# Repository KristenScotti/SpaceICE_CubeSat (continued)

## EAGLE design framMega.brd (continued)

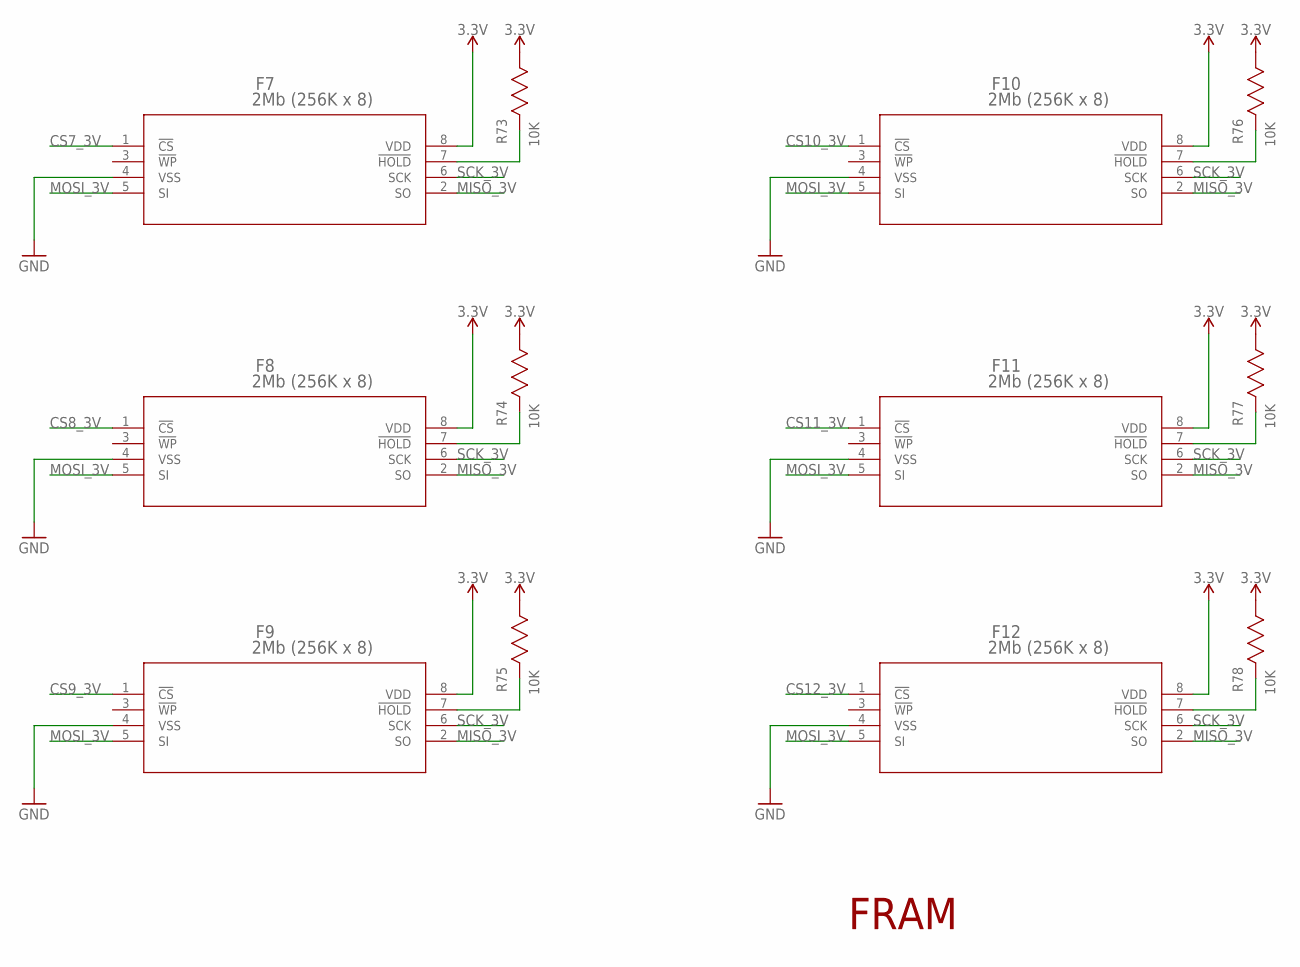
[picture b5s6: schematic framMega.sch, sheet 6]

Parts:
F7, F8, F9, F10, F11, F12: 2Mb (256K x 8); FRAM_MB85RS2MTA_FPT-8P-M09
R73, R74, R75, R76, R77, R78: 10K; RC0603N

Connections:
3.3V: F7.8 (VDD), F8.8 (VDD), F9.8 (VDD), F10.8 (VDD), F11.8 (VDD), F12.8 (VDD), R73.1 (11), R74.1 (11), R75.1 (11), R76.1 (11), R77.1 (11), R78.1 (11); also elsewhere on the board
CS7_3V: F7.1 (!CS); also elsewhere on the board
CS8_3V: F8.1 (!CS); also elsewhere on the board
CS9_3V: F9.1 (!CS); also elsewhere on the board
CS10_3V: F10.1 (!CS); also elsewhere on the board
CS11_3V: F11.1 (!CS); also elsewhere on the board
CS12_3V: F12.1 (!CS); also elsewhere on the board
GND: F7.4 (VSS), F8.4 (VSS), F9.4 (VSS), F10.4 (VSS), F11.4 (VSS), F12.4 (VSS); also elsewhere on the board
MISO_3V: F7.2 (SO), F8.2 (SO), F9.2 (SO), F10.2 (SO), F11.2 (SO), F12.2 (SO); also elsewhere on the board
MOSI_3V: F7.5 (SI), F8.5 (SI), F9.5 (SI), F10.5 (SI), F11.5 (SI), F12.5 (SI); also elsewhere on the board
unnamed: F7.7 (!HOLD), R73.2 (22)
unnamed: F10.7 (!HOLD), R76.2 (22)
unnamed: F8.7 (!HOLD), R74.2 (22)
unnamed: F11.7 (!HOLD), R77.2 (22)
unnamed: F9.7 (!HOLD), R75.2 (22)
unnamed: F12.7 (!HOLD), R78.2 (22)
SCK_3V: F7.6 (SCK), F8.6 (SCK), F9.6 (SCK), F10.6 (SCK), F11.6 (SCK), F12.6 (SCK); also elsewhere on the board

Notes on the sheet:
FRAM

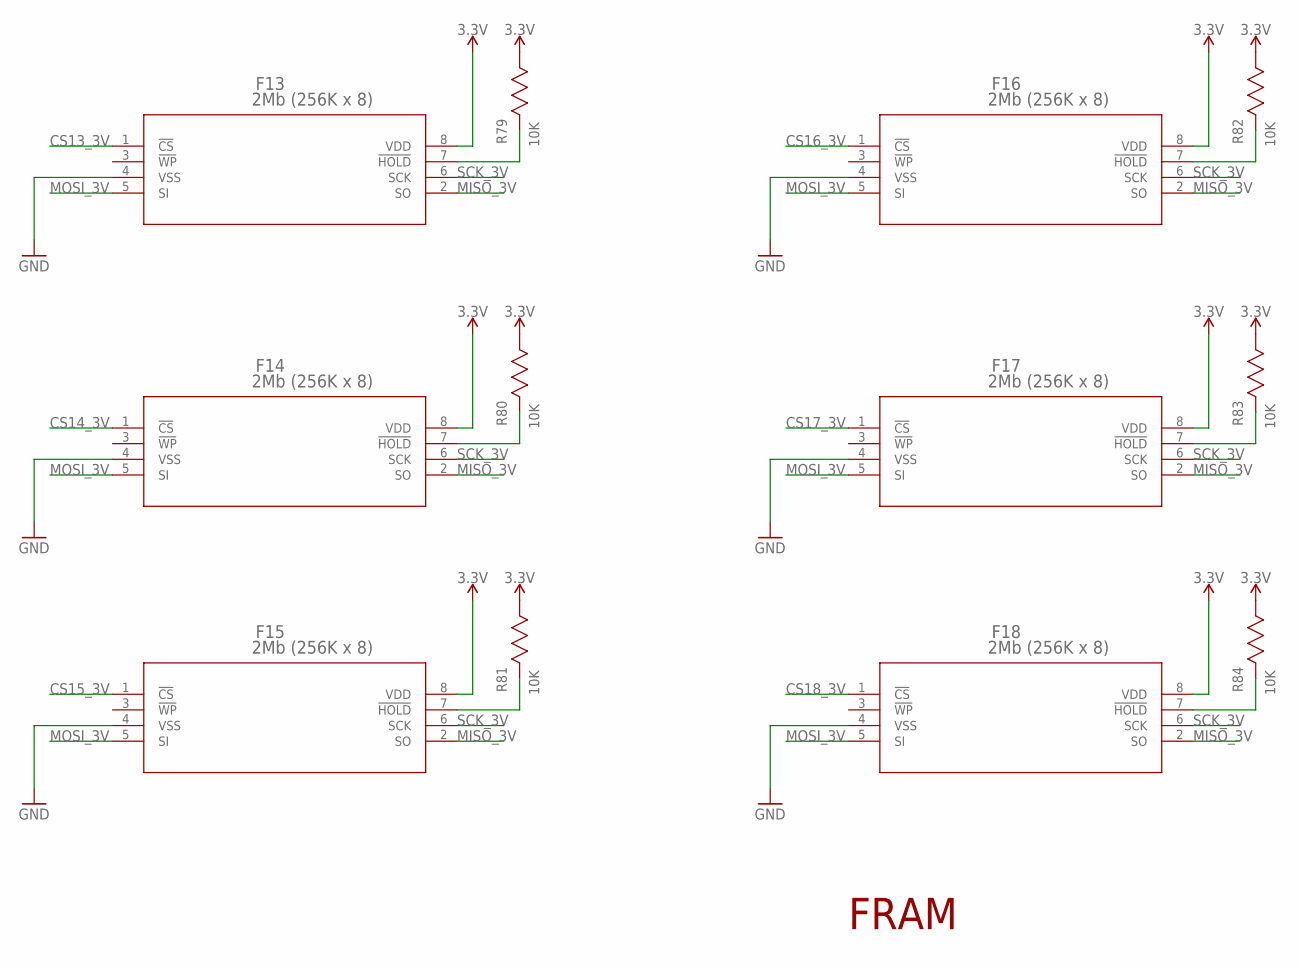
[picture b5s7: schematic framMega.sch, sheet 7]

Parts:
F13, F14, F15, F16, F17, F18: 2Mb (256K x 8); FRAM_MB85RS2MTA_FPT-8P-M09
R79, R80, R81, R82, R83, R84: 10K; RC0603N

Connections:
3.3V: F13.8 (VDD), F14.8 (VDD), F15.8 (VDD), F16.8 (VDD), F17.8 (VDD), F18.8 (VDD), R79.1 (11), R80.1 (11), R81.1 (11), R82.1 (11), R83.1 (11), R84.1 (11); also elsewhere on the board
CS13_3V: F13.1 (!CS); also elsewhere on the board
CS14_3V: F14.1 (!CS); also elsewhere on the board
CS15_3V: F15.1 (!CS); also elsewhere on the board
CS16_3V: F16.1 (!CS); also elsewhere on the board
CS17_3V: F17.1 (!CS); also elsewhere on the board
CS18_3V: F18.1 (!CS); also elsewhere on the board
GND: F13.4 (VSS), F14.4 (VSS), F15.4 (VSS), F16.4 (VSS), F17.4 (VSS), F18.4 (VSS); also elsewhere on the board
MISO_3V: F13.2 (SO), F14.2 (SO), F15.2 (SO), F16.2 (SO), F17.2 (SO), F18.2 (SO); also elsewhere on the board
MOSI_3V: F13.5 (SI), F14.5 (SI), F15.5 (SI), F16.5 (SI), F17.5 (SI), F18.5 (SI); also elsewhere on the board
unnamed: F13.7 (!HOLD), R79.2 (22)
unnamed: F16.7 (!HOLD), R82.2 (22)
unnamed: F14.7 (!HOLD), R80.2 (22)
unnamed: F17.7 (!HOLD), R83.2 (22)
unnamed: F15.7 (!HOLD), R81.2 (22)
unnamed: F18.7 (!HOLD), R84.2 (22)
SCK_3V: F13.6 (SCK), F14.6 (SCK), F15.6 (SCK), F16.6 (SCK), F17.6 (SCK), F18.6 (SCK); also elsewhere on the board

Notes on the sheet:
FRAM

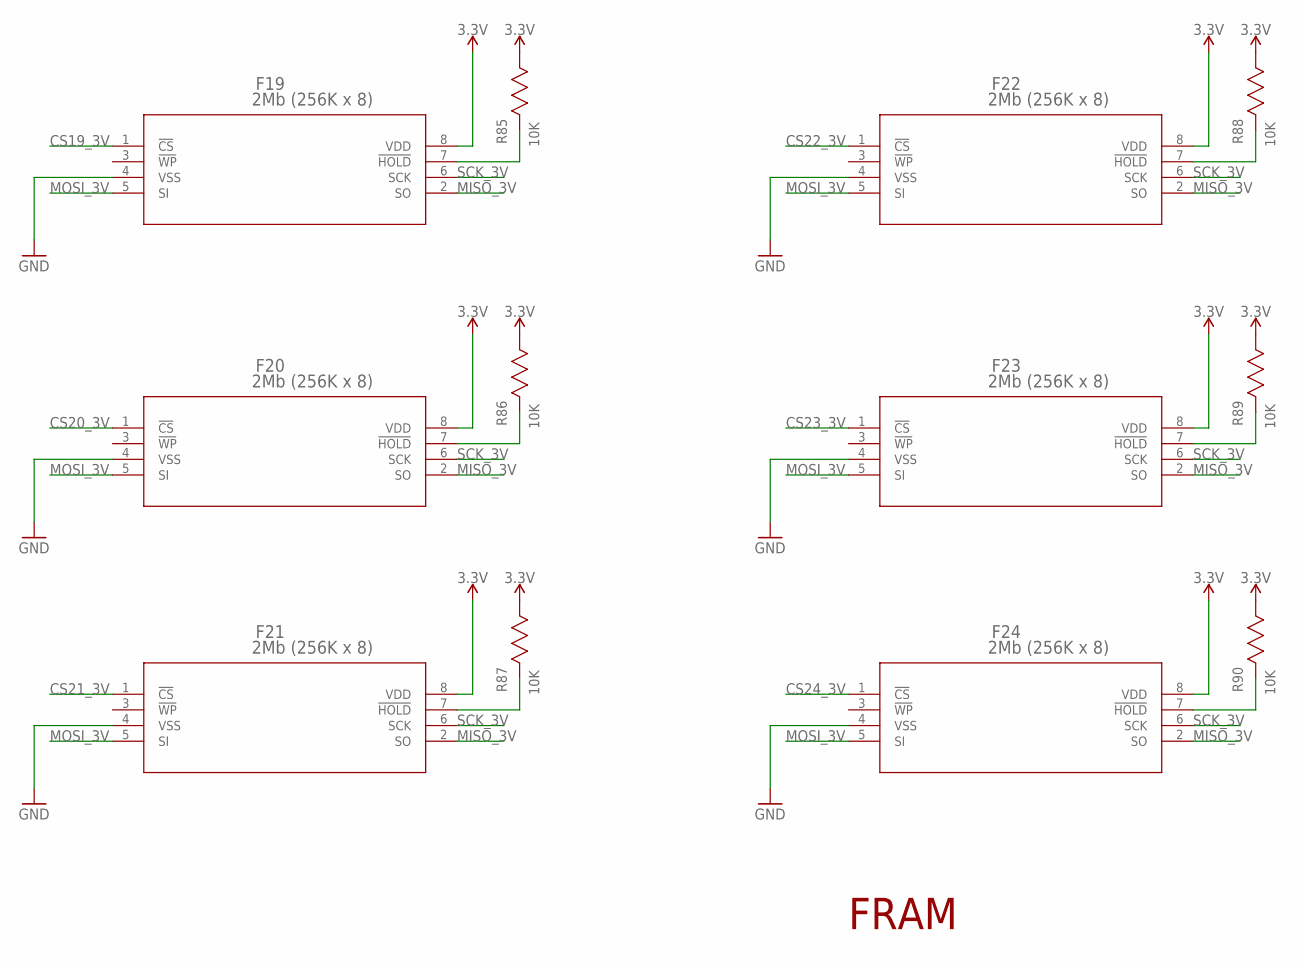
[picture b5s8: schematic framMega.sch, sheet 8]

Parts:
F19, F20, F21, F22, F23, F24: 2Mb (256K x 8); FRAM_MB85RS2MTA_FPT-8P-M09
R85, R86, R87, R88, R89, R90: 10K; RC0603N

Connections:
3.3V: F19.8 (VDD), F20.8 (VDD), F21.8 (VDD), F22.8 (VDD), F23.8 (VDD), F24.8 (VDD), R85.1 (11), R86.1 (11), R87.1 (11), R88.1 (11), R89.1 (11), R90.1 (11); also elsewhere on the board
CS19_3V: F19.1 (!CS); also elsewhere on the board
CS20_3V: F20.1 (!CS); also elsewhere on the board
CS21_3V: F21.1 (!CS); also elsewhere on the board
CS22_3V: F22.1 (!CS); also elsewhere on the board
CS23_3V: F23.1 (!CS); also elsewhere on the board
CS24_3V: F24.1 (!CS); also elsewhere on the board
GND: F19.4 (VSS), F20.4 (VSS), F21.4 (VSS), F22.4 (VSS), F23.4 (VSS), F24.4 (VSS); also elsewhere on the board
MISO_3V: F19.2 (SO), F20.2 (SO), F21.2 (SO), F22.2 (SO), F23.2 (SO), F24.2 (SO); also elsewhere on the board
MOSI_3V: F19.5 (SI), F20.5 (SI), F21.5 (SI), F22.5 (SI), F23.5 (SI), F24.5 (SI); also elsewhere on the board
unnamed: F19.7 (!HOLD), R85.2 (22)
unnamed: F22.7 (!HOLD), R88.2 (22)
unnamed: F20.7 (!HOLD), R86.2 (22)
unnamed: F23.7 (!HOLD), R89.2 (22)
unnamed: F21.7 (!HOLD), R87.2 (22)
unnamed: F24.7 (!HOLD), R90.2 (22)
SCK_3V: F19.6 (SCK), F20.6 (SCK), F21.6 (SCK), F22.6 (SCK), F23.6 (SCK), F24.6 (SCK); also elsewhere on the board

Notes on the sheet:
FRAM

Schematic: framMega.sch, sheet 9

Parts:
F25, F26, F27, F28, F29, F30: 2Mb (256K x 8); FRAM_MB85RS2MTA_FPT-8P-M09
R91, R92, R93, R94, R95, R96: 10K; RC0603N

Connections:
3.3V: F25.8 (VDD), F26.8 (VDD), F27.8 (VDD), F28.8 (VDD), F29.8 (VDD), F30.8 (VDD), R91.1 (11), R92.1 (11), R93.1 (11), R94.1 (11), R95.1 (11), R96.1 (11); also elsewhere on the board
CS25_3V: F25.1 (!CS); also elsewhere on the board
CS26_3V: F26.1 (!CS); also elsewhere on the board
CS27_3V: F27.1 (!CS); also elsewhere on the board
CS28_3V: F28.1 (!CS); also elsewhere on the board
CS29_3V: F29.1 (!CS); also elsewhere on the board
CS30_3V: F30.1 (!CS); also elsewhere on the board
GND: F25.4 (VSS), F26.4 (VSS), F27.4 (VSS), F28.4 (VSS), F29.4 (VSS), F30.4 (VSS); also elsewhere on the board
MISO_3V: F25.2 (SO), F26.2 (SO), F27.2 (SO), F28.2 (SO), F29.2 (SO), F30.2 (SO); also elsewhere on the board
MOSI_3V: F25.5 (SI), F26.5 (SI), F27.5 (SI), F28.5 (SI), F29.5 (SI), F30.5 (SI); also elsewhere on the board
unnamed: F25.7 (!HOLD), R91.2 (22)
unnamed: F28.7 (!HOLD), R94.2 (22)
unnamed: F26.7 (!HOLD), R92.2 (22)
unnamed: F29.7 (!HOLD), R95.2 (22)
unnamed: F27.7 (!HOLD), R93.2 (22)
unnamed: F30.7 (!HOLD), R96.2 (22)
SCK_3V: F25.6 (SCK), F26.6 (SCK), F27.6 (SCK), F28.6 (SCK), F29.6 (SCK), F30.6 (SCK); also elsewhere on the board

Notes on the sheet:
FRAM

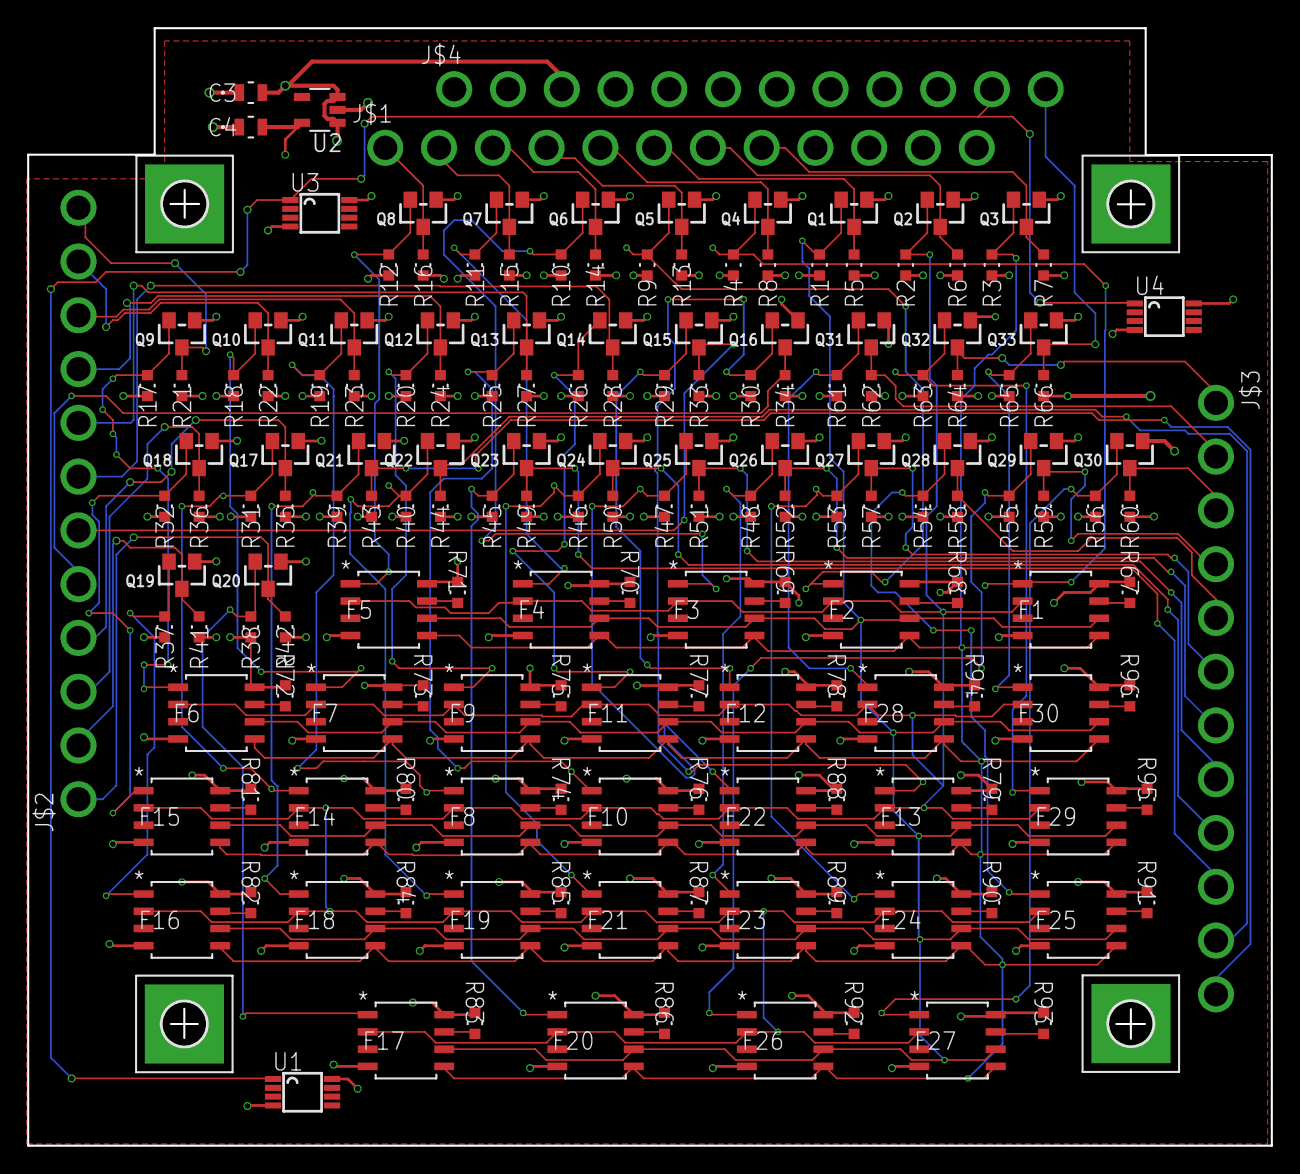
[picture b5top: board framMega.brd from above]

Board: 4 copper layers, 91.6 x 82.3 mm, 173 parts (0 on the bottom side), 100 nets.

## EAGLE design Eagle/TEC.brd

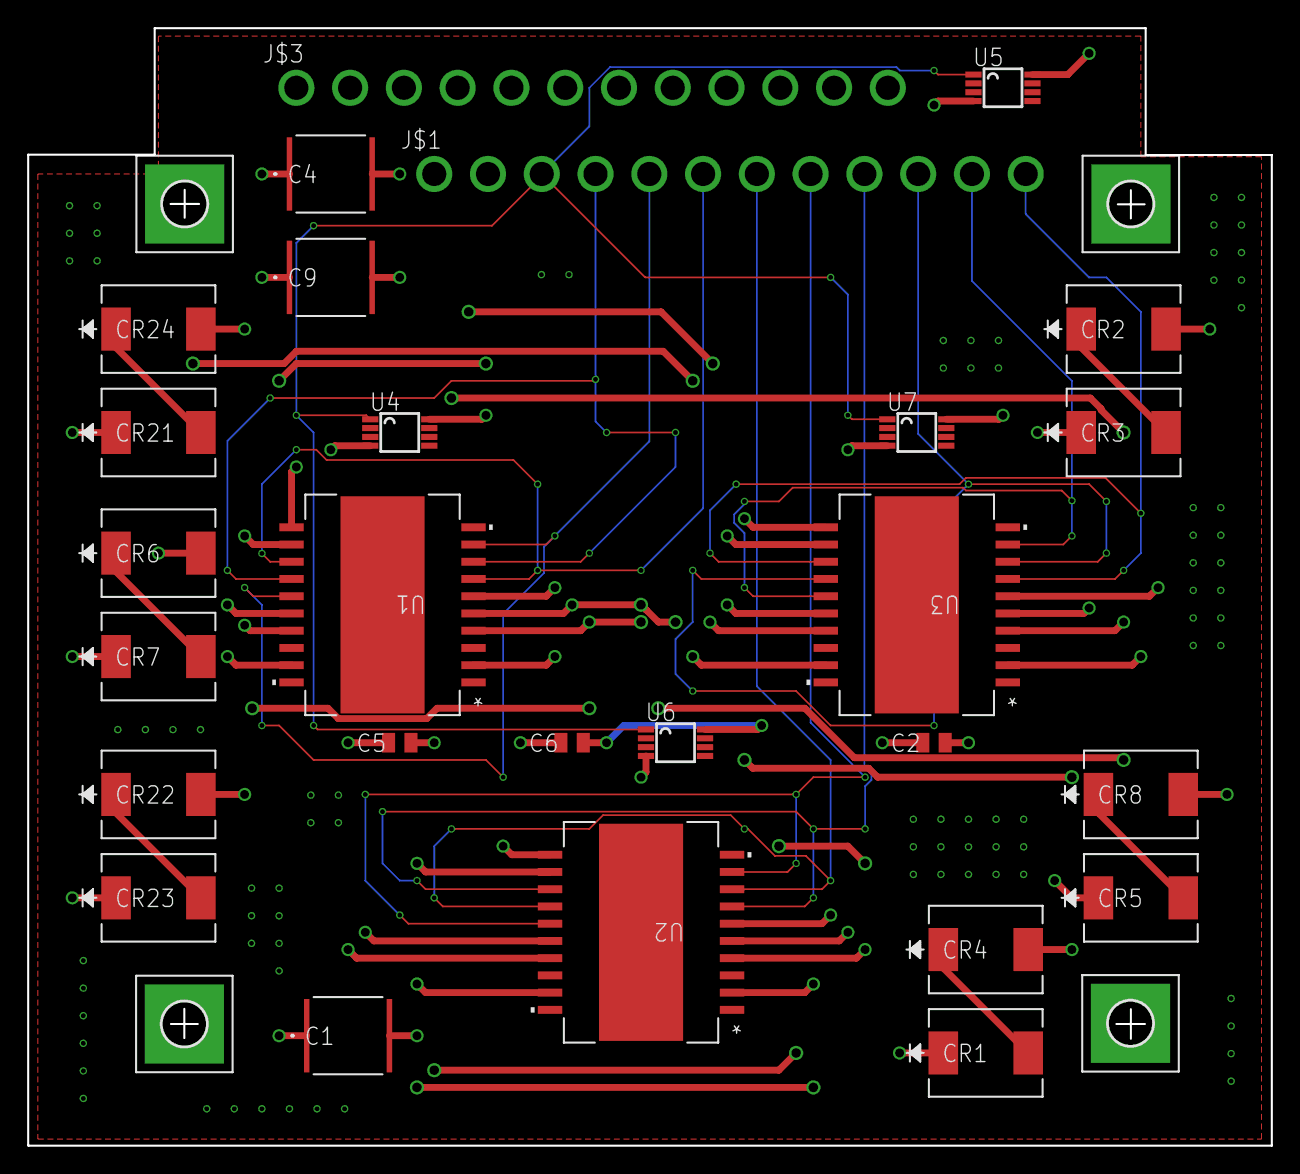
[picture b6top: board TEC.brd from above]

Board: 4 copper layers, 91.6 x 82.3 mm, 31 parts (0 on the bottom side), 25 nets.

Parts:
C1, C4, C9: 47uF; CAP_5750
C2, C5, C6: 1uF; YAG_CC0805
CR1, CR2, CR3, CR4, CR5, CR6, CR7, CR8, CR21, CR22, CR23, CR24: DIODE_400V_5A
H1, H2, H3, H4: MOUNT-PAD-SQUARE3.2; 3,2-PAD-SQUARE
J$1, J$3: WIREPOST; WIREWRAPPOST
U1, U2, U3: L298P013TR; POWERSO-20
U4, U5, U6, U7: DS18B20U+T&R; SOP65P500X110-8N

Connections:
5V: C2.2, C5.2, C6.2, J$3.10, U1.12, U2.12, U3.12, U4.8, U5.8, U6.8, U7.8
GND: C1.1, C2.1, C4.1, C5.1, C6.1, C9.1, CR2.2, CR4.2, CR6.2, CR8.2, CR22.2, CR24.2, J$3.1, J$3.2, J$3.9, J$3.11, U1.2, U1.11, U1.19, U2.2, U2.11, U2.19, U3.2, U3.11, U3.19, U4.4, U5.4, U6.4, U7.4
unnamed: CR1.2, CR4.1
unnamed: CR2.1, CR3.2
unnamed: CR5.2, CR8.1
unnamed: CR6.1, CR7.2
unnamed: CR21.2, CR24.1
unnamed: CR22.1, CR23.2
TEC1_ENABLE: J$1.4, U1.8, U1.14
TEC1_INPUT1: J$1.6, U1.7, U1.13
TEC1_INPUT2: J$1.5, U1.9, U1.15
TEC1_OUT1: J$3.8, U1.4, U1.17
TEC1_OUT2: J$3.7, U1.5, U1.16
TEC2_ENABLE: J$1.7, U2.8, U2.14
TEC2_INPUT1: J$1.9, U2.7, U2.13
TEC2_INPUT2: J$1.8, U2.9, U2.15
TEC2_OUT1: J$3.6, U2.4, U2.17
TEC2_OUT2: J$3.5, U2.5, U2.16
TEC3_ENABLE: J$1.10, U3.8, U3.14
TEC3_INPUT1: J$1.12, U3.7, U3.13
TEC3_INPUT2: J$1.11, U3.9, U3.15
TEC3_OUT1: J$3.4, U3.4, U3.17
TEC3_OUT2: J$3.3, U3.5, U3.16
TEMP: J$1.3, U4.1, U5.1, U6.1, U7.1
VIN: C1.2, C4.2, C9.2, CR1.1, CR3.1, CR5.1, CR7.1, CR21.1, CR23.1, J$3.12, U1.6, U2.6, U3.6

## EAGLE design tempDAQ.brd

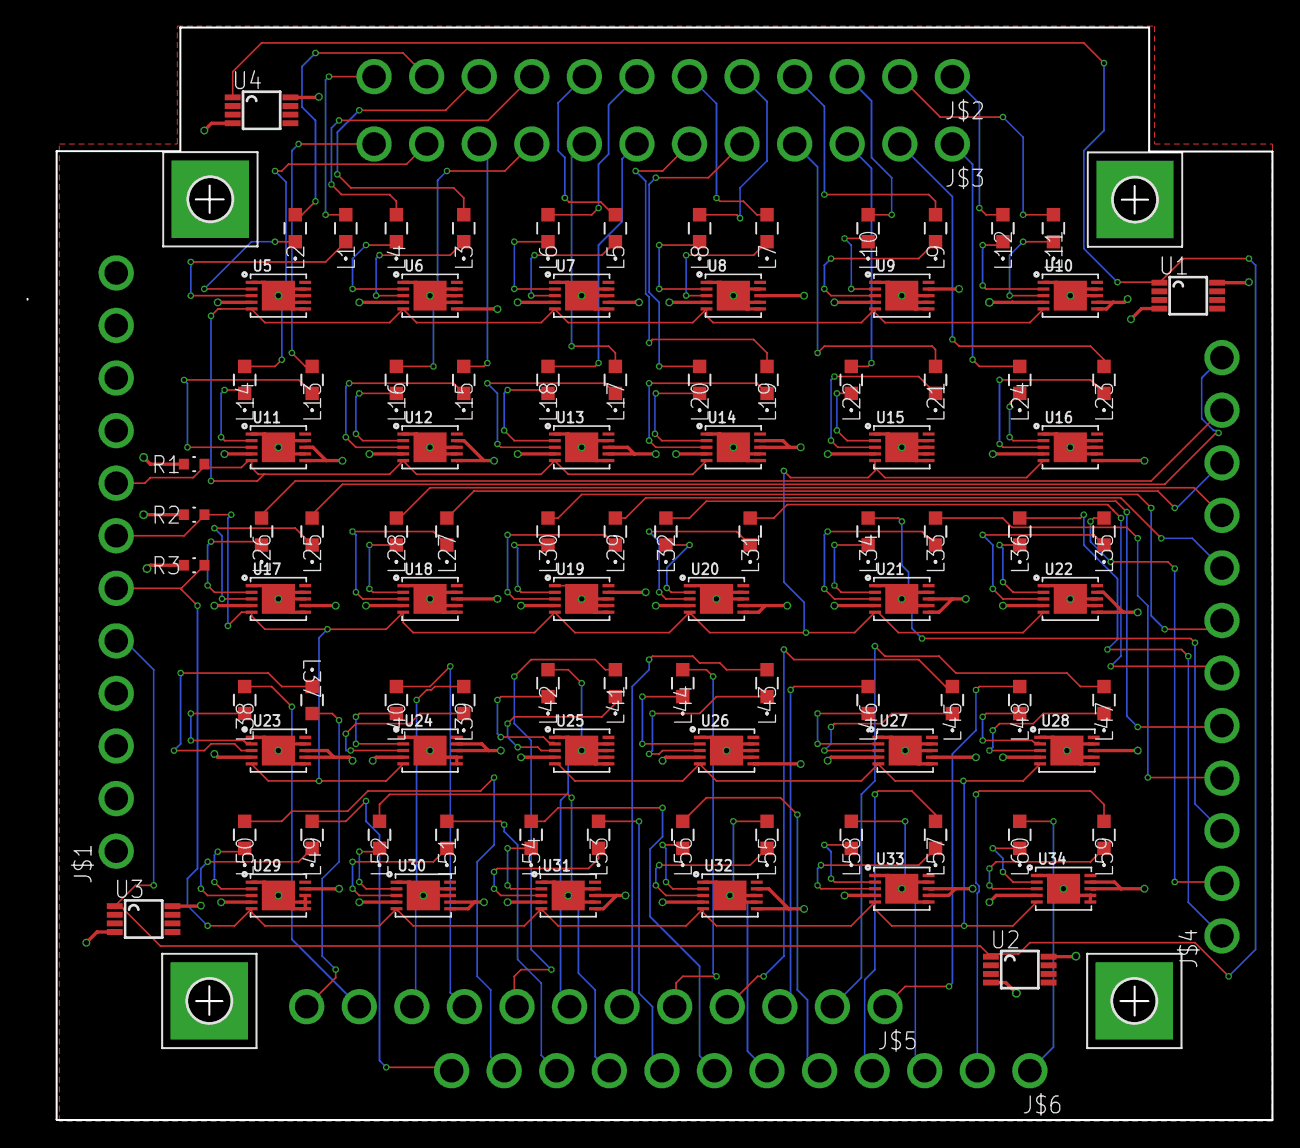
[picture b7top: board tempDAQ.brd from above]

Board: 4 copper layers, 93.8 x 82.3 mm, 107 parts (0 on the bottom side), 126 nets.

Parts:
H1, H2, H3, H4: MOUNT-PAD-SQUARE3.2; 3,2-PAD-SQUARE
J$1, J$2, J$3, J$4, J$5, J$6: WIREPOST; WIREWRAPPOST
L1, L2, L3, L4, L5, L6, L7, L8, L9, L10, L11, L12, L13, L14, L15, L16, L17, L18, L19, L20, L21, L22, L23, L24, L25, L26, L27, L28, L29, L30, L31, L32, L33, L34, L35, L36, L37, L38, L39, L40, L41, L42, L43, L44, L45, L46, L47, L48, L49, L50, L51, L52, L53, L54, L55, L56, L57, L58, L59, L60: FERRITE; IND_BOURNS_MH2029
R1, R2, R3: 4.7K; RC0603N
U1, U2, U3, U4: DS18B20U+T&R; SOP65P500X110-8N
U5, U6, U7, U8, U9, U10, U11, U12, U13, U14, U15, U16, U17, U18, U19, U20, U21, U22, U23, U24, U25, U26, U27, U28, U29, U30, U31, U32, U33, U34: MAX31850; TDFN10_3X4MM

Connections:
3.3V: J$1.12, R1.1, R2.1, R3.1, U1.8, U2.8, U3.8, U4.8, U5.4, U6.4, U6.6, U7.4, U7.7, U8.4, U8.8, U9.4, U9.9, U10.4, U10.6, U10.7, U11.4, U11.6, U11.8, U12.4, U12.6, U12.9, U13.4, U13.7, U13.8, U14.4, U14.8, U14.9, U15.4, U16.4, U16.6, U17.4, U17.7, U18.4, U18.8, U19.4, U19.9, U20.4, U20.6, U20.7, U21.4, U21.6, U21.8, U22.4, U22.6, U22.9, U23.4, U23.7, U23.8, U24.4, U24.8, U24.9, U25.4, U26.4, U26.6, U27.4, U27.7, U28.4, U28.8, U29.4, U29.9, U30.4, U30.6, U30.7, U31.4, U31.6, U31.8, U32.4, U32.6, U32.9, U33.4, U33.7, U33.8, U34.4, U34.8, U34.9
DATA1: J$1.8, R1.2, U5.5, U6.5, U7.5, U8.5, U9.5, U10.5, U11.5, U12.5, U13.5, U14.5
DATA2: J$1.7, R2.2, U15.5, U16.5, U17.5, U18.5, U19.5, U20.5, U21.5, U22.5, U23.5, U24.5
DATA3: J$1.6, R3.2, U25.5, U26.5, U27.5, U28.5, U29.5, U30.5, U31.5, U32.5, U33.5, U34.5
GND: J$1.9, J$1.10, J$1.11, U1.4, U2.4, U3.4, U4.4, U5.1, U5.6, U5.7, U5.8, U5.9, U5.THERMAL, U6.1, U6.7, U6.8, U6.9, U6.THERMAL, U7.1, U7.6, U7.8, U7.9, U7.THERMAL, U8.1, U8.6, U8.7, U8.9, U8.THERMAL, U9.1, U9.6, U9.7, U9.8, U9.THERMAL, U10.1, U10.8, U10.9, U10.THERMAL, U11.1, U11.7, U11.9, U11.THERMAL, U12.1, U12.7, U12.8, U12.THERMAL, U13.1, U13.6, U13.9, U13.THERMAL, U14.1, U14.6, U14.7, U14.THERMAL, U15.1, U15.6, U15.7, U15.8, U15.9, U15.THERMAL, U16.1, U16.7, U16.8, U16.9, U16.THERMAL, U17.1, U17.6, U17.8, U17.9, U17.THERMAL, U18.1, U18.6, U18.7, U18.9, U18.THERMAL, U19.1, U19.6, U19.7, U19.8, U19.THERMAL, U20.1, U20.8, U20.9, U20.THERMAL, U21.1, U21.7, U21.9, U21.THERMAL, U22.1, U22.7, U22.8, U22.THERMAL, U23.1, U23.6, U23.9, U23.THERMAL, U24.1, U24.6, U24.7, U24.THERMAL, U25.1, U25.6, U25.7, U25.8, U25.9, U25.THERMAL, U26.1, U26.7, U26.8, U26.9, U26.THERMAL, U27.1, U27.6, U27.8, U27.9, U27.THERMAL, U28.1, U28.6, U28.7, U28.9, U28.THERMAL, U29.1, U29.6, U29.7, U29.8, U29.THERMAL, U30.1, U30.8, U30.9, U30.THERMAL, U31.1, U31.7, U31.9, U31.THERMAL, U32.1, U32.7, U32.8, U32.THERMAL, U33.1, U33.6, U33.9, U33.THERMAL, U34.1, U34.6, U34.7, U34.THERMAL
unnamed: L21.1, U15.3
unnamed: L22.1, U15.2
unnamed: L23.1, U16.3
unnamed: L24.1, U16.2
unnamed: L26.1, U17.2
unnamed: L25.1, U17.3
unnamed: L27.1, U18.3
unnamed: L28.1, U18.2
unnamed: L29.1, U19.3
unnamed: L30.1, U19.2
unnamed: L31.1, U20.3
unnamed: L32.1, U20.2
unnamed: L33.1, U21.3
unnamed: L34.1, U21.2
unnamed: L35.1, U22.3
unnamed: L36.1, U22.2
unnamed: L1.1, U5.3
unnamed: L37.1, U23.3
unnamed: L38.1, U23.2
unnamed: L39.1, U24.3
unnamed: L40.1, U24.2
unnamed: L2.1, U5.2
unnamed: L3.1, U6.3
unnamed: L4.1, U6.2
unnamed: L6.1, U7.2
unnamed: L5.1, U7.3
unnamed: L7.1, U8.3
unnamed: L8.1, U8.2
unnamed: L9.1, U9.3
unnamed: L10.1, U9.2
unnamed: L11.1, U10.3
unnamed: L12.1, U10.2
unnamed: L13.1, U11.3
unnamed: L14.1, U11.2
unnamed: L15.1, U12.3
unnamed: L16.1, U12.2
unnamed: L17.1, U13.3
unnamed: L18.1, U13.2
unnamed: L19.1, U14.3
unnamed: L20.1, U14.2
unnamed: L41.1, U25.3
unnamed: L42.1, U25.2
unnamed: L43.1, U26.3
unnamed: L44.1, U26.2
unnamed: L46.1, U27.2
unnamed: L45.1, U27.3
unnamed: L47.1, U28.3
unnamed: L48.1, U28.2
unnamed: L49.1, U29.3
unnamed: L50.1, U29.2
unnamed: L51.1, U30.3
unnamed: L52.1, U30.2
unnamed: L53.1, U31.3
unnamed: L54.1, U31.2
unnamed: L55.1, U32.3
unnamed: L56.1, U32.2
unnamed: L57.1, U33.3
unnamed: L58.1, U33.2
unnamed: L59.1, U34.3
unnamed: L60.1, U34.2
T1+: J$2.12, L1.2
T1-: J$2.11, L2.2
T2+: J$2.10, L3.2
T2-: J$2.9, L4.2
T3+: J$2.8, L5.2
T3-: J$2.7, L6.2
T4+: J$2.6, L7.2
T4-: J$2.5, L8.2
T5+: J$2.4, L9.2
T5-: J$2.3, L10.2
T6+: J$2.2, L11.2
T6-: J$2.1, L12.2
T7+: J$3.12, L13.2
T7-: J$3.11, L14.2
T8+: J$3.10, L15.2
T8-: J$3.9, L16.2
T9+: J$3.8, L17.2
T9-: J$3.7, L18.2
T10+: J$3.6, L19.2
T10-: J$3.5, L20.2
T11+: J$3.4, L21.2
T11-: J$3.3, L22.2
T12+: J$3.2, L23.2
T12-: J$3.1, L24.2
T13+: J$4.12, L25.2
T13-: J$4.11, L26.2
T14+: J$4.10, L27.2
T14-: J$4.9, L28.2
T15+: J$4.8, L29.2
T15-: J$4.7, L30.2
T16+: J$4.6, L31.2
T16-: J$4.5, L32.2
T17+: J$4.4, L33.2
T17-: J$4.3, L34.2
T18+: J$4.2, L35.2
T18-: J$4.1, L36.2
T19+: J$5.12, L37.2
T19-: J$5.11, L38.2
T20+: J$5.10, L39.2
T20-: J$5.9, L40.2
T21+: J$5.8, L41.2
T21-: J$5.7, L42.2
T22+: J$5.6, L43.2
T22-: J$5.5, L44.2
T23+: J$5.4, L45.2
T23-: J$5.3, L46.2
T24+: J$5.2, L47.2
T24-: J$5.1, L48.2
T25+: J$6.12, L49.2
T25-: J$6.11, L50.2
T26+: J$6.10, L51.2
T26-: J$6.9, L52.2
T27+: J$6.8, L53.2
T27-: J$6.7, L54.2
T28+: J$6.6, L55.2
T28-: J$6.5, L56.2
T29+: J$6.4, L57.2
T29-: J$6.3, L58.2
T30+: J$6.2, L59.2
T30-: J$6.1, L60.2
TEMP: J$1.5, U1.1, U2.1, U3.1, U4.1

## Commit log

2018-04-01 Create atmega2560
2018-04-01 Create nano
